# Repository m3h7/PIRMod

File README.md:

# Umbau von 230V Bewegungsmeldern auf 24V
- [Bewegungsmelder-Umbau mit Taktgeber](PIR2mod/README.md)
- [Bewegungsmelder-Umbau](PIR1mod/README.md) (veraltet)
- [Steinel IS1](steinel_is1/README.md) (veraltet)

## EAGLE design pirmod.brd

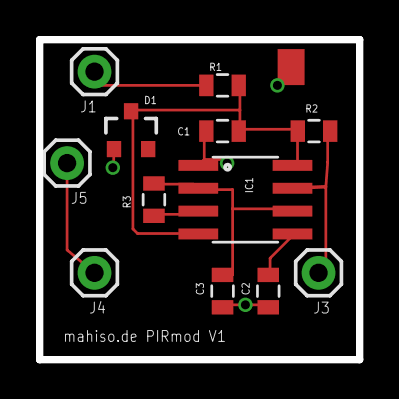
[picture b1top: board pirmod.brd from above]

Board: 2 copper layers, 17.8 x 17.8 mm, 13 parts (0 on the bottom side), 8 nets.

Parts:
C1, C2, C3: 100n; 0805
D1: BCX84-C12; SOT23-3
IC1: TLC555; SO08
J1: 22V; 1X01
J2: GND; PAD-1.5X4.5
J3: TACT; 1X01
J4: OUT-PIR; 1X01
J5: OUT; 1X01
R1: 2,2k; 0805
R2: 4,7k; 0805
R3: 27k; 0805

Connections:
12V: C1.1, D1.3, IC1.4, IC1.8, R1.2, R2.2
GND: C1.2, C2.2, C3.2, D1.1, IC1.1, J2.P$1
unnamed: J4.1, J5.1
unnamed: C3.1, IC1.2, IC1.6, R3.1
unnamed: J1.1, R1.1
unnamed: C2.1, IC1.5
unnamed: IC1.3, R3.2
unnamed: IC1.7, J3.1, R2.1

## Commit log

2015-03-18 Initial
2015-04-14 Endstufe entfernt
2015-04-17 Erstes Routing.
2015-09-06 Backup
2015-09-06 Change resistor r6
2015-09-20 Bauteilnummerierung geändert.
2015-10-21 Remove old image exports
2015-10-21 Move Eagle project. Add PIR modification pictures
2015-10-21 Add README and LICENSE
2017-08-09 Steinel IS1; Übernahme aus wiki
2017-08-09 Schreibfehler korrigiert.
2018-12-29 Übername PIR2 aus wiki
2018-12-30 Übernahme aus Wiki, Umbau alte Version
2018-12-30 Linkreihenfolge geändert

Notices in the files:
parts and their libraries:
SparkFun-Capacitors: Licensing: Creative Commons ShareAlike 4.0 International - https://creativecommons.org/licenses/by-sa/4.0
